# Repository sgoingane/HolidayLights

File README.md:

# HolidayLights

ESP8266 firmware for controlling a holiday LED strip from a browser. It provides themed LED effects, scheduled operation, sunrise/sunset-based clock colors, runtime logs, and OTA firmware updates.

## Requirements

- Arduino IDE 2.3.6
- ESP8266 board support from the Boards Manager
- Libraries: `Adafruit NeoPixel`, `ArduinoJson`, `ElegantOTA`, and `NTPClient`
- An ESP8266 board and a compatible NeoPixel strip

`DNSServer` and BearSSL are provided by the ESP8266 core; they are not separate library dependencies.

## Initial Setup

1. Open the project in Arduino IDE.
2. Install the ESP8266 board package and libraries listed above.
3. Configure `Secrets.h` for your Wi-Fi network. The sketch checks for these exact macro names:

	```cpp
	#define WIFI_SSD "your-wifi-ssid"
	#define WIFI_PASSWD "your-wifi-password"
	```

	Keep real credentials private; do not publish them in a repository or screenshot.
4. Connect the ESP8266 over USB. Select **Generic ESP8266 Module** (or the matching board), choose the correct port, and upload the sketch.
5. Open the Serial Monitor at 115200 baud. In station mode, use the printed IP address to open the control page from a device on the same Wi-Fi network.

## Network Modes

- **Configured Wi-Fi:** When both `WIFI_SSD` and `WIFI_PASSWD` are defined, the device joins that network. Open `http://<device-ip>/` on the same network.
- **Setup hotspot:** If either home Wi-Fi credential macro is absent, the device starts the open `DropItLikeItsHotspot` network. Wildcard DNS directs HTTP requests to the OTA page. If the captive prompt does not open, visit `http://192.168.4.1/update` manually.
- AP-mode firmware exposes ElegantOTA only; it does not serve the lighting controls.

## Controls and Updates

- Use the slider on the main page to turn the LEDs on or off.
- Use the numbered clock buttons at 04:00 and 05:00 to toggle Relay 1 and Relay 2. The grid button toggles the LED matrix display.
- Open `/log` to view runtime messages. The log scrolls within the page.
- To move from setup mode to home Wi-Fi, compile a new build with both `WIFI_SSD` and `WIFI_PASSWD` defined. While the device is still running setup-mode firmware, connect to its hotspot, open `http://192.168.4.1/update`, and upload the new build. After reboot, it joins the configured home network and serves the lighting controls.
- OTA is available only in AP setup builds. A build with home Wi-Fi credentials does not expose OTA; future updates require USB upload or another AP-mode provisioning build.
- ElegantOTA identifies this firmware as `HolidayLights`, version `1.0.0`. Update the version passed to `ElegantOTA.setFWVersion()` in `OTA.h` for each firmware release.
- OTA uses HTTP and is unauthenticated on the open setup hotspot. It is not available over the home Wi-Fi interface.

## Sunrise and Sunset

The device fetches sunrise and sunset daily from Sunrise-Sunset.org. Set `SUNRISE_LATITUDE`, `SUNRISE_LONGITUDE`, and `TIME_ZONE_OFFSET_SECONDS` in `Constants.h` for the installation location. The current offset is a fixed UTC−7; locations with daylight saving time need their offset adjusted seasonally. If the API request fails, the firmware retains its fallback times.

## HTTPS and Captive Portal Notes

The captive portal uses HTTP because devices must be able to reach it before accepting a certificate. Wildcard DNS cannot transparently intercept HTTPS: browsers reject a certificate that does not match the requested host. The ESP8266 core includes BearSSL, but a usable HTTPS server also needs a private key and certificate trusted by each client. The current ElegantOTA integration requires the non-secure `ESP8266WebServer`, so adding HTTPS for the control page would leave OTA on a separate HTTP server. HTTPS is not enabled in this firmware; do not assume the current HTTP pages or OTA uploads are encrypted.

## Notes

- Intended for a trusted local network, not public internet access.
- Designed for one holiday lighting controller and LED strip.

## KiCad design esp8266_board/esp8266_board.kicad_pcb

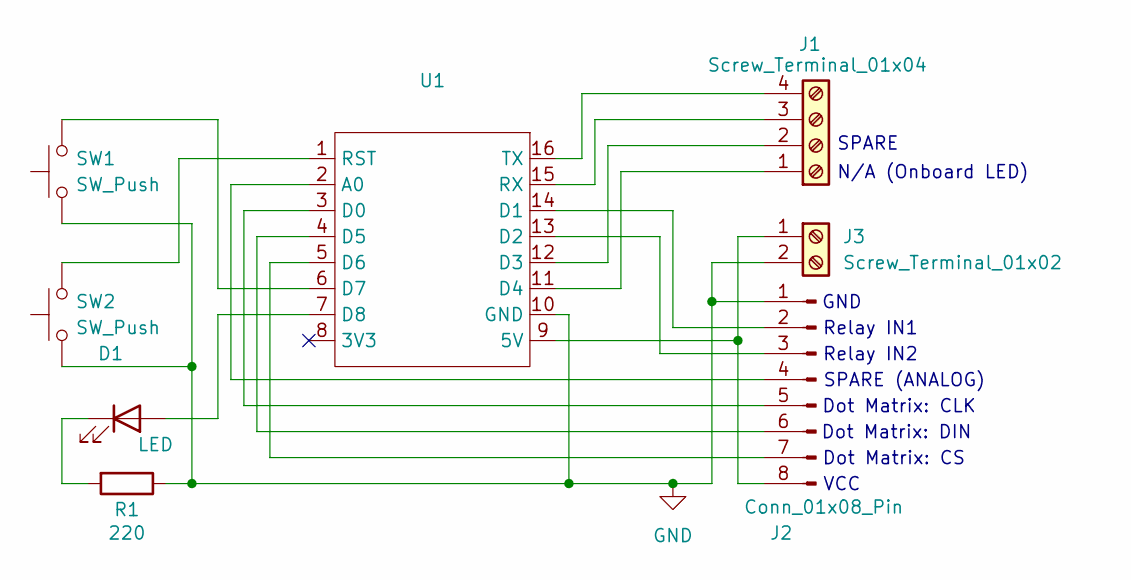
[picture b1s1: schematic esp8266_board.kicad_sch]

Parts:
D1: LED; LED_D5.0mm
J1: Screw_Terminal_01x04; TerminalBlock_Xinya_XY308-2.54-4P_1x04_P2.54mm_Horizontal
J2: Conn_01x08_Pin; PinHeader_1x08_P2.54mm_Vertical
J3: Screw_Terminal_01x02; TerminalBlock_Xinya_XY308-2.54-2P_1x02_P2.54mm_Horizontal
R1: 220; R_Axial_DIN0204_L3.6mm_D1.6mm_P2.54mm_Vertical
SW1, SW2: SW_Push; SW_PUSH_6mm_H5mm
U1: Generic_ESP8266MOD

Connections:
GND: J2.1, J3.2, R1.1, SW1.1, SW2.1, U1.10 (GND)
unnamed: D1.2 (A), U1.7 (D8)
unnamed: D1.1 (K), R1.2
unnamed: J1.1, U1.11 (D4)
unnamed: J1.2, U1.12 (D3)
unnamed: J1.3, U1.15 (RX)
unnamed: J1.4, U1.16 (TX)
unnamed: J2.2, U1.14 (D1)
unnamed: J2.3, U1.13 (D2)
unnamed: J2.4, U1.2 (A0)
unnamed: J2.5, U1.3 (D0)
unnamed: J2.6, U1.4 (D5)
unnamed: J2.7, U1.5 (D6)
unnamed: J2.8, J3.1, U1.9 (5V)
unnamed: SW1.2, U1.6 (D7)
unnamed: SW2.2, U1.1 (RST)

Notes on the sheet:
Relay IN1
Dot Matrix: CLK
Relay IN2
VCC
Dot Matrix: CS
SPARE (ANALOG)
Dot Matrix: DIN
GND
N/A (Onboard LED)
SPARE

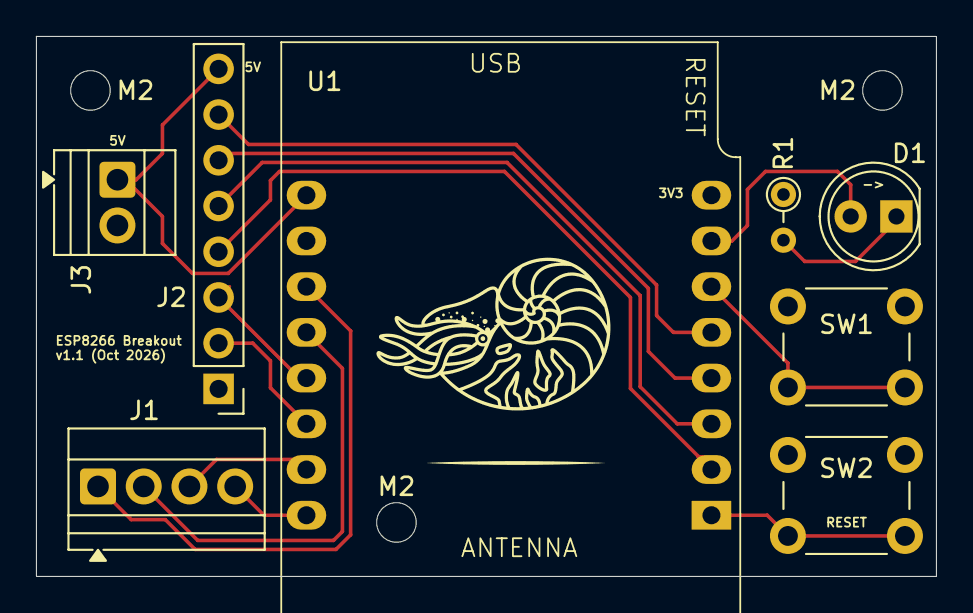
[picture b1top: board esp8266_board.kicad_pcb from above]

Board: 2 copper layers, 50.0 x 30.0 mm, 11 parts (0 on the bottom side), 16 nets.

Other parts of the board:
M2, M2#2, M2#3: MountingHole_2.2mm_M2

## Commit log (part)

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2025-10-20 Initial commit, working OTA and basic LED control
2025-10-20 Basic on/off and added helper function file
2025-10-21 Initial web control functionality
2025-10-21 Centering button on webpage
2025-11-09 thanksgiving mods, new log page, some code reorg
2025-11-10 fixed off bug, timing correct, need to trim log size
